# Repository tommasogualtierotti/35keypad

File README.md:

# 35keypad
35 keys programmable Macropad based on RP2040 MCU from Raspberry Pi, running [KMK firmware](https://github.com/KMKfw/kmk_firmware)
### Version 1

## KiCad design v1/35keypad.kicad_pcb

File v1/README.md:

# 35keypad
35 keys programmable Macropad based on RP2040 MCU from Raspberry Pi, running [KMK firmware](https://github.com/KMKfw/kmk_firmware)

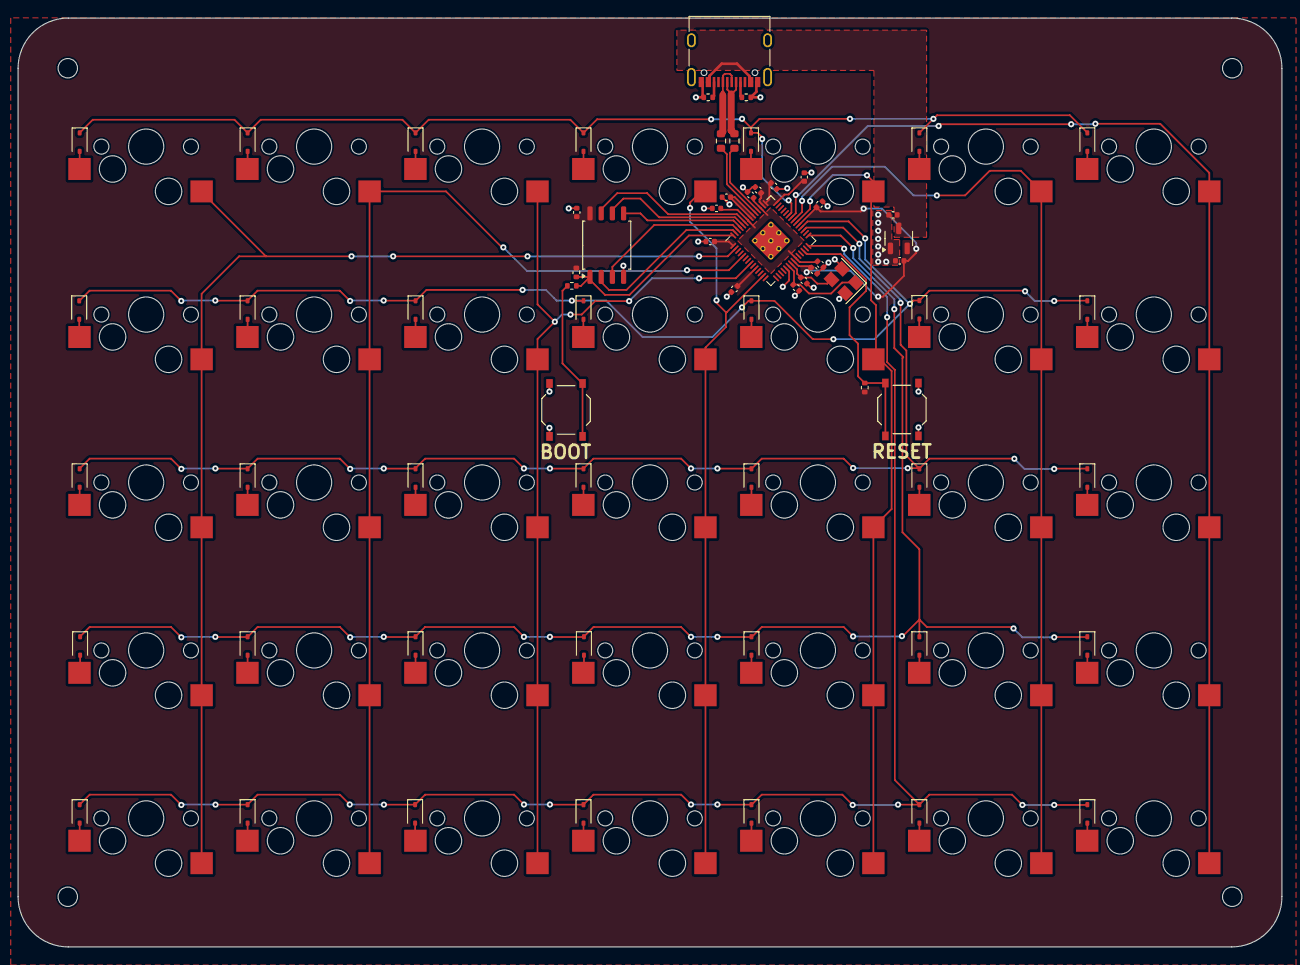
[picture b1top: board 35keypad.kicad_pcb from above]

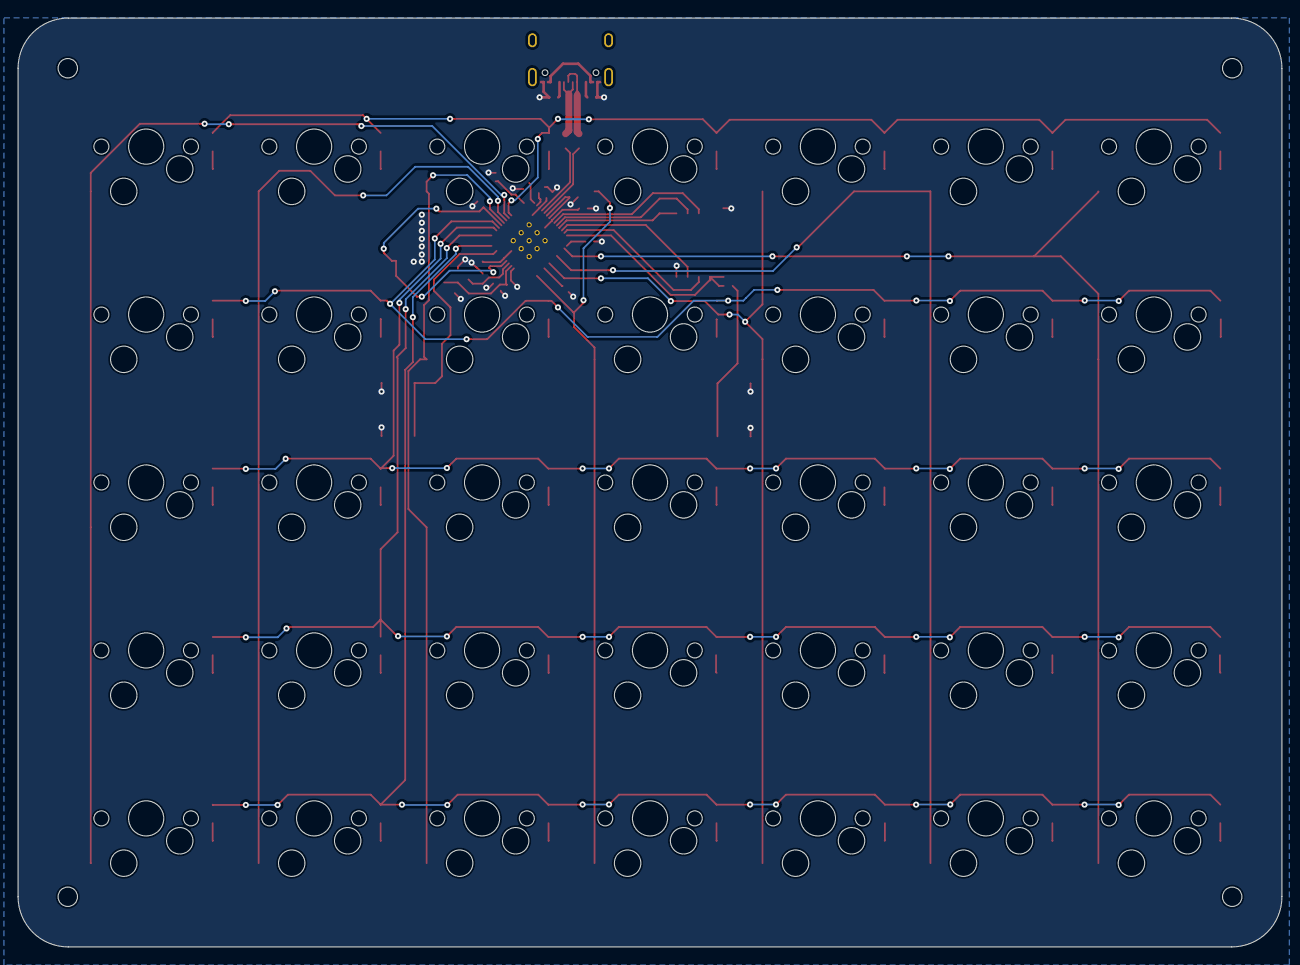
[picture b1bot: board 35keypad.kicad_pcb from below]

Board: 2 copper layers, 143.4 x 105.4 mm, 104 parts (35 on the bottom side), 67 nets.

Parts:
C1, C3, C4, C6, C7, C9, C10, C13, C14, C16: 100n; C_0402_1005Metric
C2, C5, C8, C11: 1u; C_0402_1005Metric
C12, C15: 30p; C_0402_1005Metric
D1, D2, D3, D4, D5, D6, D7, D8, D9, D10, D11, D12, D13, D14, D15, D16, D17, D18, D19, D20, D21, D22, D23, D24, D25, D26, D27, D28, D29, D30, D31, D32, D33, D34, D35: D; D_SOD-323
H1, H2, H3, H4: MountingHole; MountingHole_2.2mm_M2
J1: USB_C_Receptacle_USB2.0; USB_C_Receptacle_XKB_U262-16XN-4BVC11
R1: 10k; R_0402_1005Metric
R2, R3: 5k1; R_0402_1005Metric
R4: DNP_10k; R_0402_1005Metric
R5: 1k; R_0402_1005Metric
R6, R7: 27; R_0603_1608Metric
SW1, SW2: SW_SPST; SW_Push_1P1T_XKB_TS-1187A
SW3: KEY_1_00; Kailh_socket_MX
SW4: KEY_5_10; Kailh_socket_MX
SW5, SW6, SW7: KEY_9_20; Kailh_socket_MX
SW8: KEY_2_01; Kailh_socket_MX
SW9: KEY_6_11; Kailh_socket_MX
SW10, SW11, SW12: KEY_10_21; Kailh_socket_MX
SW13: KEY_3_02; Kailh_socket_MX
SW14: KEY_7_12; Kailh_socket_MX
SW15, SW16, SW17: KEY_11_22; Kailh_socket_MX
SW18, SW23, SW24, SW25, SW26, SW27, SW28, SW33, SW34, SW35, SW36, SW37: KEY_4_03; Kailh_socket_MX
SW19, SW29: KEY_8_13; Kailh_socket_MX
SW20, SW21, SW22, SW30, SW31, SW32: KEY_12_23; Kailh_socket_MX
U1: W25Q128JVS; SOIC-8_5.23x5.23mm_P1.27mm
U2: RP2040; RP2040-QFN-56
U3: NCP1117-3.3_SOT223; SOT-23-3
Y1: 12MHz; Crystal_SMD_3225-4Pin_3.2x2.5mm

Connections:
+1V1: C1.2, C2.1, C3.1, U2.23 (DVDD), U2.45 (VREG_VOUT), U2.50 (DVDD)
+3V3: C4.1, C6.1, C7.1, C8.1, C9.1, C10.1, C11.1, C13.1, C14.1, C16.1, R1.2, R4.2, U1.8 (VCC), U2.1 (IOVDD), U2.10 (IOVDD), U2.22 (IOVDD), U2.33 (IOVDD), U2.42 (IOVDD), U2.43 (ADC_AVDD), U2.44 (VREG_IN), U2.48 (USB_VDD), U2.49 (IOVDD), U3.2 (VO)
/COL_0: SW3.1, SW4.1, SW5.1, SW6.1, SW7.1, U2.36 (GPIO24)
/COL_1: SW8.1, SW9.1, SW10.1, SW11.1, SW12.1, U2.35 (GPIO23)
/COL_2: SW13.1, SW14.1, SW15.1, SW16.1, SW17.1, U2.34 (GPIO22)
/COL_3: SW18.1, SW19.1, SW20.1, SW21.1, SW22.1, U2.13 (GPIO10)
/COL_4: SW23.1, SW24.1, SW25.1, SW26.1, SW27.1, U2.8 (GPIO6)
/COL_5: SW28.1, SW29.1, SW30.1, SW31.1, SW32.1, U2.5 (GPIO3)
/COL_6: SW33.1, SW34.1, SW35.1, SW36.1, SW37.1, U2.2 (GPIO0)
/QSPI_SCLK: U1.6 (CLK), U2.52 (QSPI_SCLK)
/QSPI_SD0: U1.5 (DI(IO0)), U2.53 (QSPI_SD0)
/QSPI_SD1: U1.2 (DO(IO1)), U2.55 (QSPI_SD1)
/QSPI_SD2: U1.3 (IO2), U2.54 (QSPI_SD2)
/QSPI_SD3: U1.7 (IO3), U2.51 (QSPI_SD3)
/QSPI_SS: R4.1, R5.2, U1.1 (~CS), U2.56 (QSPI_SS)
/ROW_0: D1.1 (K), D6.1 (K), D11.1 (K), D16.1 (K), D21.1 (K), D26.1 (K), D31.1 (K), U2.37 (GPIO25)
/ROW_1: D2.1 (K), D7.1 (K), D12.1 (K), D17.1 (K), D22.1 (K), D27.1 (K), D32.1 (K), U2.32 (GPIO21)
/ROW_2: D3.1 (K), D8.1 (K), D13.1 (K), D18.1 (K), D23.1 (K), D28.1 (K), D33.1 (K), U2.31 (GPIO20)
/ROW_3: D4.1 (K), D9.1 (K), D14.1 (K), D19.1 (K), D24.1 (K), D29.1 (K), D34.1 (K), U2.29 (GPIO18)
/ROW_4: D5.1 (K), D10.1 (K), D15.1 (K), D20.1 (K), D25.1 (K), D30.1 (K), D35.1 (K), U2.28 (GPIO17)
/USB_D+: J1.A6 (D+), J1.B6 (D+), R6.2
/USB_D-: J1.A7 (D-), J1.B7 (D-), R7.2
/XIN: C12.1, U2.20 (XIN), Y1.1
/XOUT: C15.1, U2.21 (XOUT), Y1.3
/~USB_BOOT: R5.1, SW2.1 (A)
GND: C1.1, C2.2, C3.2, C4.2, C5.2, C6.2, C7.2, C8.2, C9.2, C10.2, C11.2, C12.2, C13.2, C14.2, C15.2, C16.2, J1.A1 (GND), J1.A12 (GND), J1.B1 (GND), J1.B12 (GND), R2.2, R3.2, SW1.1 (A), SW2.2 (B), U1.4 (GND), U2.19 (TESTEN), U2.57 (GND), U3.1 (GND), Y1.2, Y1.4
unnamed: D1.2 (A), SW3.2
unnamed: D2.2 (A), SW4.2
unnamed: D3.2 (A), SW5.2
unnamed: D4.2 (A), SW6.2
unnamed: D5.2 (A), SW7.2
unnamed: D6.2 (A), SW8.2
unnamed: D7.2 (A), SW9.2
unnamed: D8.2 (A), SW10.2
unnamed: D9.2 (A), SW11.2
unnamed: D10.2 (A), SW12.2
unnamed: D11.2 (A), SW13.2
unnamed: D12.2 (A), SW14.2
unnamed: D13.2 (A), SW15.2
unnamed: D14.2 (A), SW16.2
unnamed: D15.2 (A), SW17.2
unnamed: D16.2 (A), SW18.2
unnamed: D17.2 (A), SW19.2
unnamed: D18.2 (A), SW20.2
unnamed: D19.2 (A), SW21.2
unnamed: D20.2 (A), SW22.2
unnamed: D21.2 (A), SW23.2
unnamed: D22.2 (A), SW24.2
unnamed: D23.2 (A), SW25.2
unnamed: D24.2 (A), SW26.2
unnamed: D25.2 (A), SW27.2
unnamed: D26.2 (A), SW28.2
unnamed: D27.2 (A), SW29.2
unnamed: D28.2 (A), SW30.2
unnamed: D29.2 (A), SW31.2
unnamed: D30.2 (A), SW32.2
unnamed: D31.2 (A), SW33.2
unnamed: D32.2 (A), SW34.2
unnamed: D33.2 (A), SW35.2
unnamed: D34.2 (A), SW36.2
unnamed: D35.2 (A), SW37.2
unnamed: J1.A5 (CC1), R2.1
unnamed: J1.B5 (CC2), R3.1
unnamed: R1.1, SW1.2 (B), U2.26 (RUN)
unnamed: R7.1, U2.46 (USB_DM)
unnamed: R6.1, U2.47 (USB_DP)
VBUS: C5.1, J1.A4 (VBUS), J1.A9 (VBUS), J1.B4 (VBUS), J1.B9 (VBUS), U3.3 (VI)

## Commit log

2024-06-18 files: add source files for pcb design
    - add kailh hotswap socket symbol
2024-06-19 schematic: edit some footprints
2024-06-19 files: add finished pcb layout
2024-07-09 add .gitignore
2024-07-13 images: add back and front pcb image after hotswap socket soldering
2024-07-13 refactor: add v1 folder and move files
2024-07-13 feat: add v2 with fix on diodes placement and on decoupling capacitor placing
2024-07-13 docs: add README with photo of the PCB
2024-07-13 add README.md
2024-07-15 Create LICENSE
